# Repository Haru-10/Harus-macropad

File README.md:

# Harus-Turtlepad 
Turtlepad is a 9 key macropad with a rotary encoder, and an OLED Display, using KMK firmware.

#Features:
- 2 seperate pieces to make the case
- 0.91" OLED
- EC11 Rotary Encoder for Volume
- 9 Keyboard keys for Audio and General Control

  # CAD Model:
  Everything fits using M3 Bolys, and inserts.
  It contains 2 3d printed surfaces for the bottom and Top of the case, with the pcb sitting at the bottom with a usb c port open for the XIAO board to plug into.
This photo is of how the top of the case will look!

Top left has the oled (the rectangle hole), and the 3x3 matrix in the middle with a rotary encoder on the right side.

The items will also be apart, which will be updated with real life photos to make sure that everyone gets the best viewing experience!
This is the photo of the case from another angle

This is the CAD model with the PCB, there is a slit for the usb C port

  # PCB:
  Here's my schematic for the PCB, made in KICAD.

  Now Here is the layout of the actual PCB that will get printed, made up of 2 layers. It has a matrix next to a rotary encoder and an OLED.

 # Firmware
This runs entirely on KMK Firmware
- Rotary Encoder Deals with volume
- 9 keys will run different keybinds/Macros
- Oled will display days until my next competition
- These can change from a simple python file!

  # BOM:
  List of items for the hackpad
- 9x Cherry MX Switches
- 9x DSA Keycaps
- 5x M3x5x4 Heatset inserts
- 3x M3x16mm SHCS Bolts
- 2X M3x12mm SHCS Bolts
- 9x 1N4148 DO-35 Diodes.
- 1x 0.91" 128x32 OLED Display
- 1x EC11 Rotary Encoder
- 1x Xiao RP2040
- 1x Case (2x 3d printed pieces put together)
- 
  # Extra-info:
  I had to redo the entire pcb around 6 times because first I put the mcu in the middle, and then had to keep rewiring because the wires were horrible, and have learned quite a bit about pcb design.

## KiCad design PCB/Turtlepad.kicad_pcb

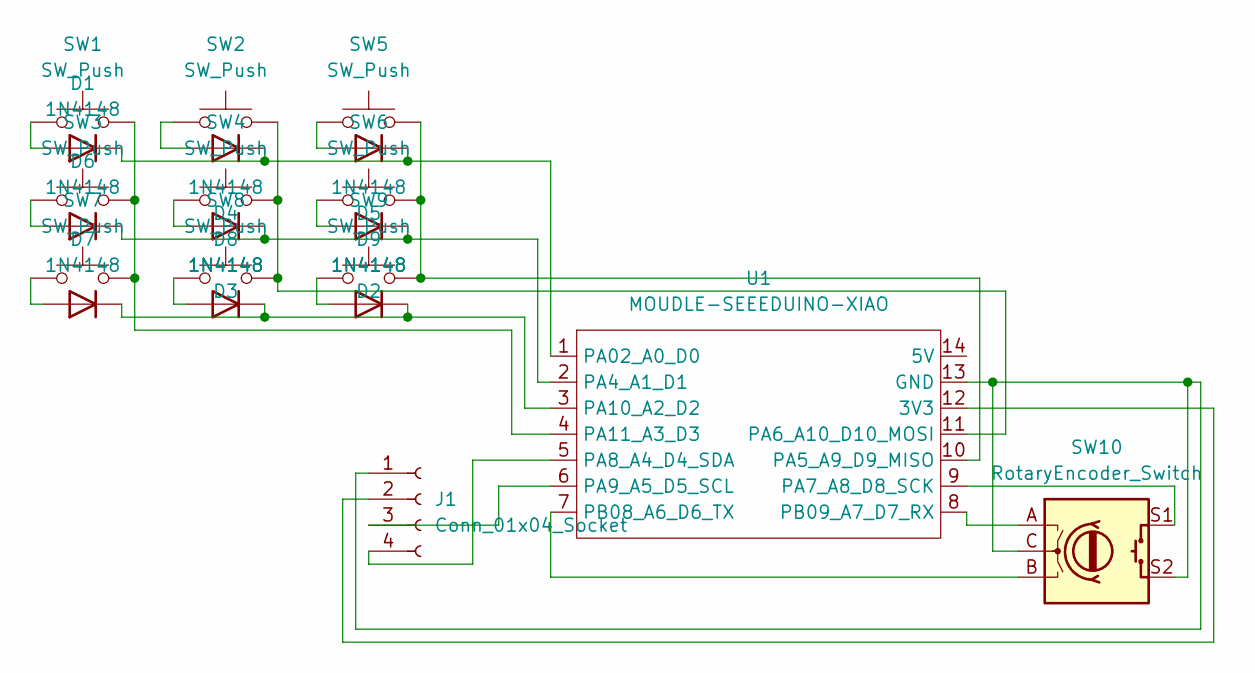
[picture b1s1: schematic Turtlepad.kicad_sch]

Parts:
D1, D2, D3, D4, D5, D6, D7, D8, D9: 1N4148; D_DO-35_SOD27_P7.62mm_Horizontal
J1: Conn_01x04_Socket; PinSocket_1x04_P2.54mm_Vertical
SW1, SW2, SW3, SW4, SW5, SW6, SW7, SW8, SW9: SW_Push; SW_Cherry_MX_1.00u_Plate
SW10: RotaryEncoder_Switch; RotaryEncoder_Alps_EC11E-Switch_Vertical_H20mm
U1: MOUDLE-SEEEDUINO-XIAO; XIAO-Generic-Hybrid-14P-2.54-21X17.8MM

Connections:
unnamed: D1.2 (A), SW1.1
unnamed: D1.1 (K), D4.1 (K), D5.1 (K), U1.1 (PA02_A0_D0)
unnamed: D2.2 (A), SW6.1
unnamed: D2.1 (K), D3.1 (K), D6.1 (K), U1.2 (PA4_A1_D1)
unnamed: D3.2 (A), SW4.1
unnamed: D4.2 (A), SW2.1
unnamed: D5.2 (A), SW5.1
unnamed: D6.2 (A), SW3.1
unnamed: D7.2 (A), SW7.1
unnamed: D7.1 (K), D8.1 (K), D9.1 (K), U1.3 (PA10_A2_D2)
unnamed: D8.2 (A), SW8.1
unnamed: D9.2 (A), SW9.1
unnamed: J1.1, SW10.C, SW10.S2, U1.13 (GND)
unnamed: J1.2, U1.12 (3V3)
unnamed: J1.3, U1.6 (PA9_A5_D5_SCL)
unnamed: J1.4, U1.5 (PA8_A4_D4_SDA)
unnamed: SW5.2, SW6.2, SW9.2, U1.10 (PA5_A9_D9_MISO)
unnamed: SW2.2, SW4.2, SW8.2, U1.11 (PA6_A10_D10_MOSI)
unnamed: SW10.S1, U1.9 (PA7_A8_D8_SCK)
unnamed: SW1.2, SW3.2, SW7.2, U1.4 (PA11_A3_D3)
unnamed: SW10.B, U1.7 (PB08_A6_D6_TX)
unnamed: SW10.A, U1.8 (PB09_A7_D7_RX)

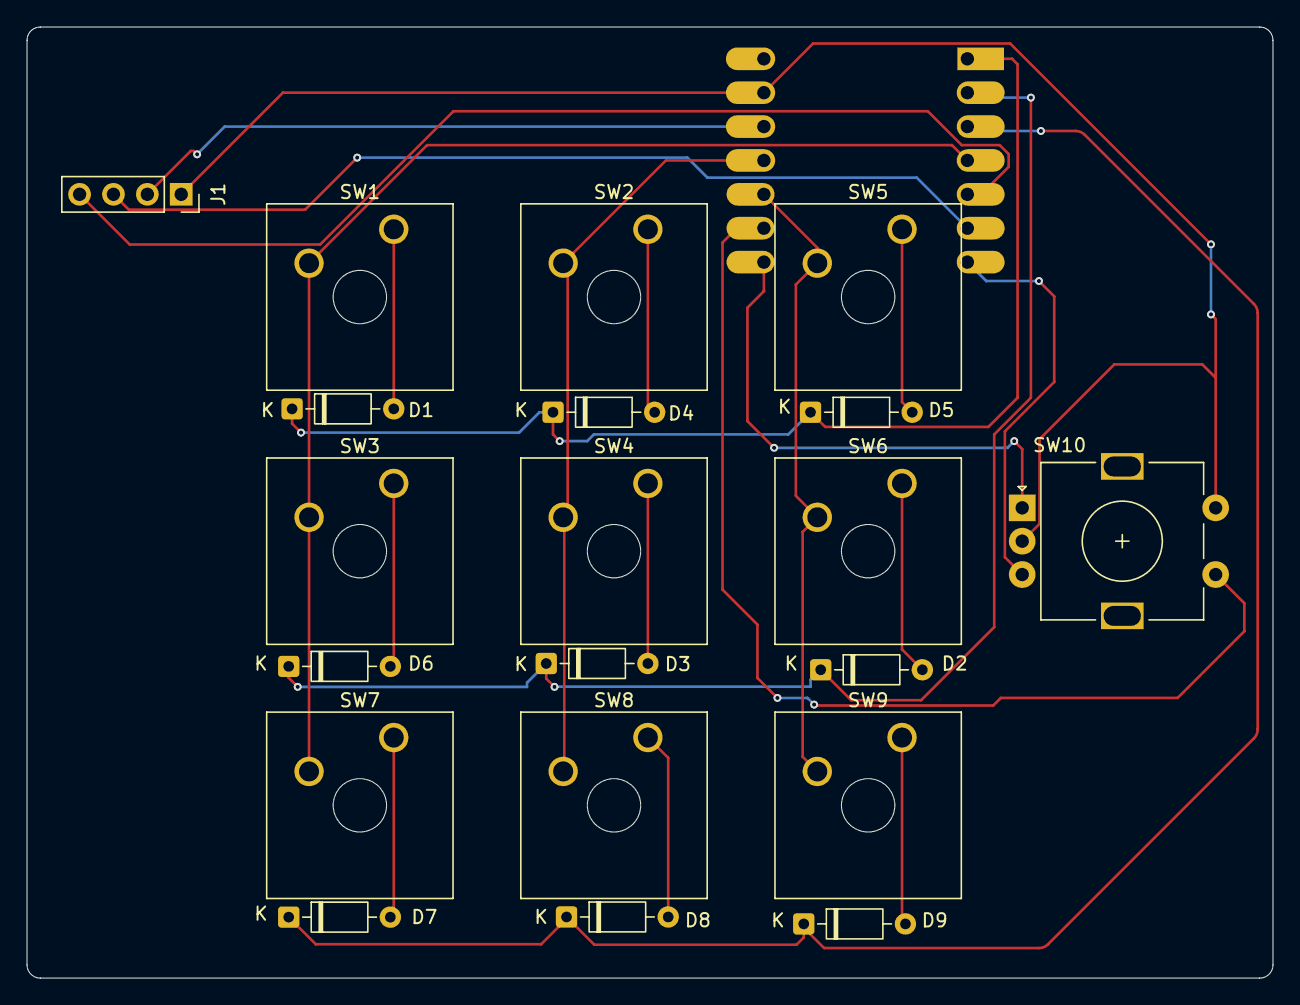
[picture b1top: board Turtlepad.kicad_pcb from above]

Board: 2 copper layers, 93.4 x 71.3 mm, 21 parts (1 on the bottom side), 22 nets.

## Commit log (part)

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2026-06-25 Update README.md
    BOM and Firmware Overview sections added.
